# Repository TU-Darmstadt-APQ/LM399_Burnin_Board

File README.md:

# ADR1399/LM399 Burnin Board
This repository contains the [KiCad](https://www.kicad.org/) schematics and design files for test board to burn in [ADR1399](https://www.analog.com/media/en/technical-documentation/data-sheets/adr1399.pdf) and [LM399](https://www.analog.com/media/en/technical-documentation/data-sheets/199399fc.pdf) voltage references.

## Contents
- [Introduction](#introduction)
- [Design Files](#design-files)
- [Related Repositories](#related-repositories)
- [Versioning](#versioning)
- [License](#license)

## Introduction
This board can support up to 20 [ADR1399](https://www.analog.com/media/en/technical-documentation/data-sheets/adr1399.pdf) or [LM399](https://www.analog.com/media/en/technical-documentation/data-sheets/199399fc.pdf) voltage references. Using a [DD-50](https://en.wikipedia.org/wiki/D-subminiature) connector, these reference can be monitored using a multiplexer and a DMM. In combination with the [2000-SCAN SSR Replacement](https://github.com/PatrickBaus/SCAN2000) up to 10 references can be scanned using a [Keithley Model 2002](https://www.tek.com/en/products/keithley/digital-multimeter/2002-series).

## Design Files
### For production
The design files required for the PCB production and assembly can be found on the [releases](../../releases) page and include the following resources:

- Schematics as a PDF
- Gerber files
- Pick & place position files
- Bill of materials as a CSV file and also as an interactive HTML version

The latest revision of those files can be found [here](../../releases/latest).

## Related Repositories
See the following repositories for more information.

- [KiCad footprints](https://github.com/PatrickBaus/footprints.pretty)
- [KiCAD schematic libraries](https://github.com/PatrickBaus/KiCad-libraries)
- [2000-SCAN SSR Replacement](https://github.com/PatrickBaus/SCAN2000)

## Versioning
I use [SemVer](http://semver.org/) for versioning. For the versions available, see the [tags](../../tags) available for this repository.

- MAJOR versions in this context mean a breaking change to the external interface of the hardware like different connectors or functions.
- MINOR versions contain changes to the hardware that only affect the inner workings of the circuit, but otherwise the performance is unaffected.
- PATCH versions do not affect the schematics or invalidate older bill of materials. These changes may include updated components (to replace obsolete parts for example), an updated silkscreen, or fixed typos.

## License
This work is released under the CERN-OHL-W
See [https://ohwr.org/cern_ohl_w_v2.pdf](https://ohwr.org/cern_ohl_w_v2.pdf) or the included LICENSE file for more information.

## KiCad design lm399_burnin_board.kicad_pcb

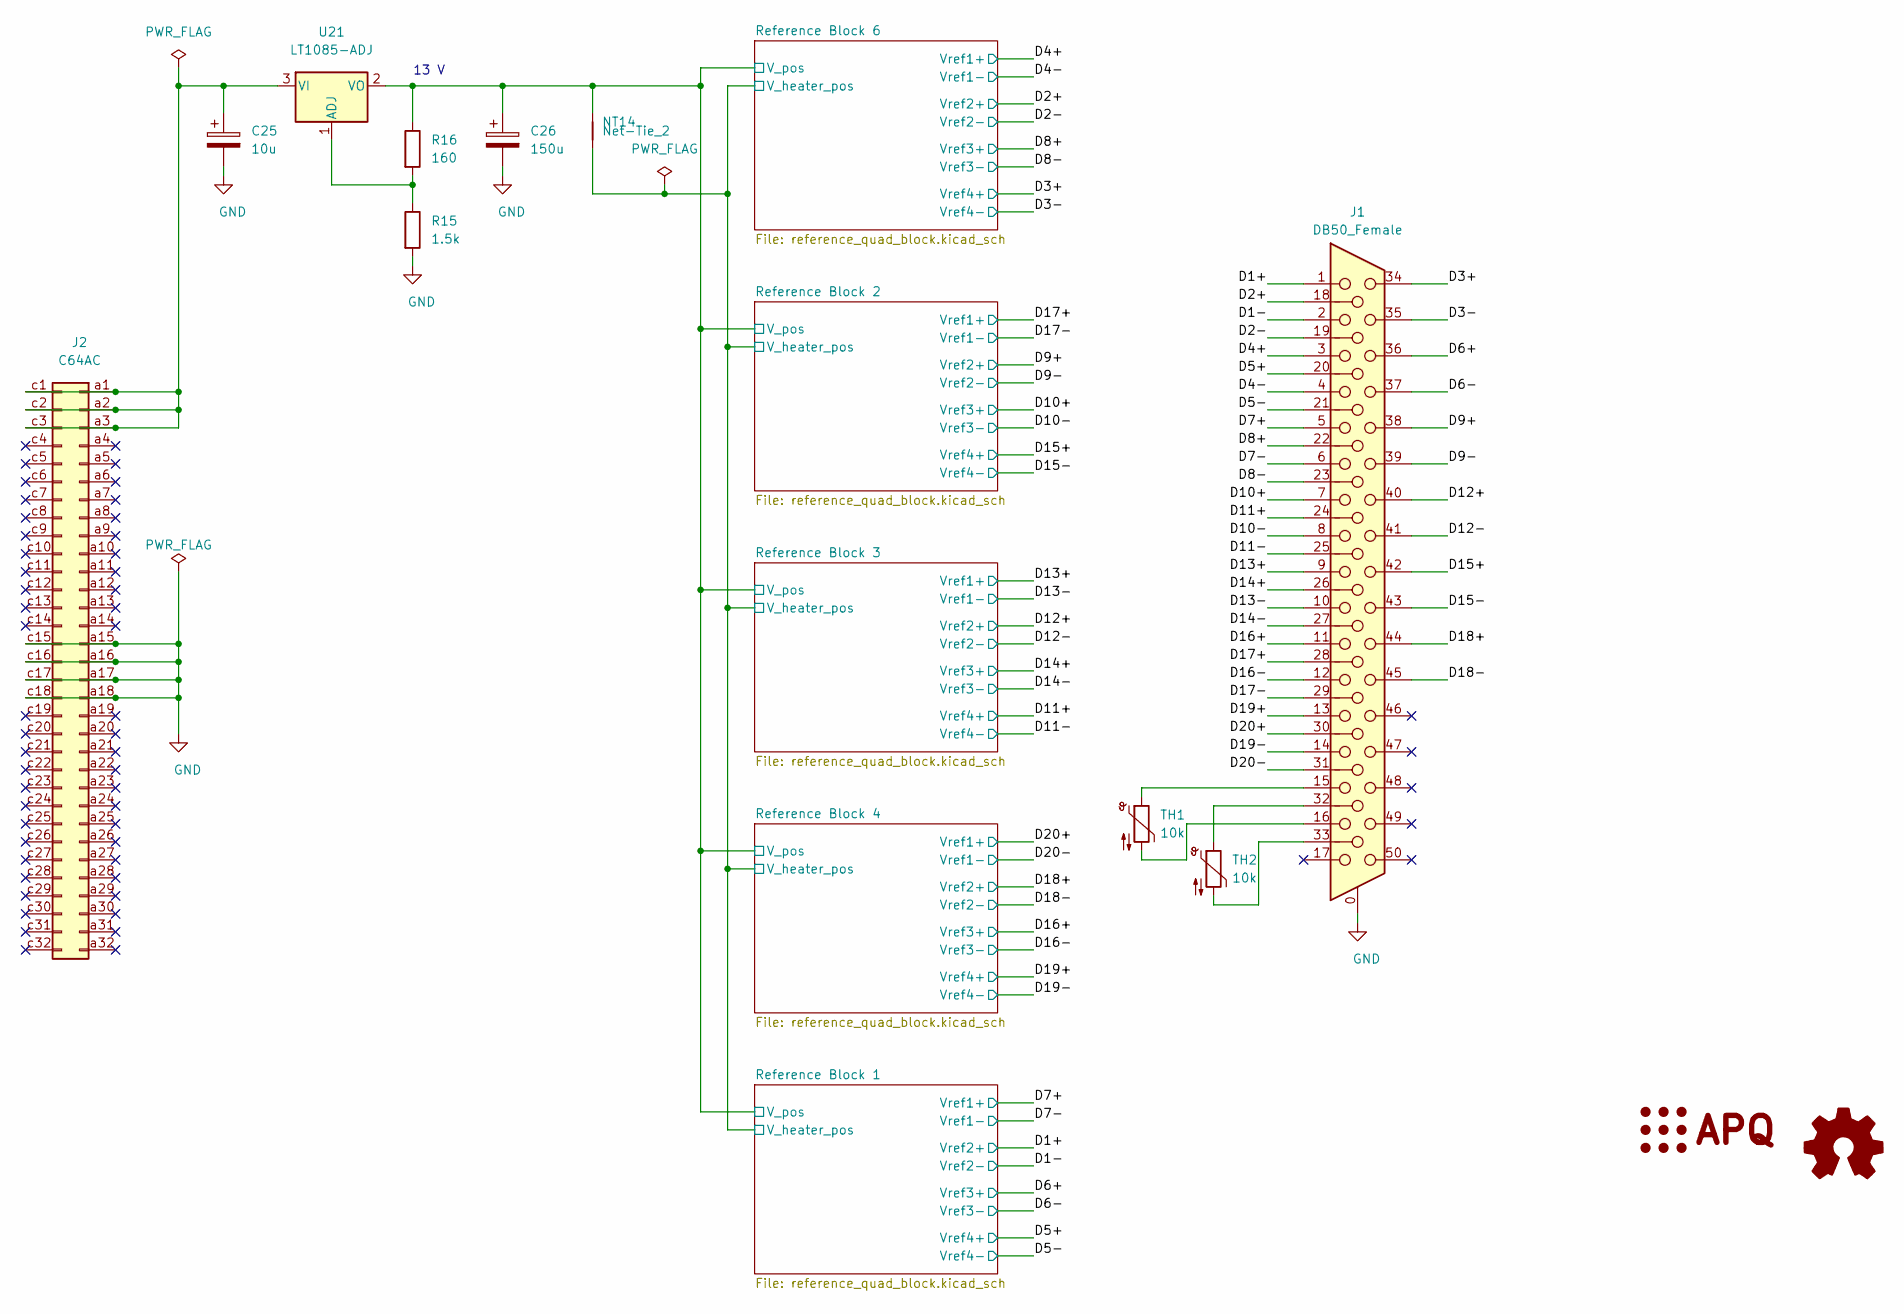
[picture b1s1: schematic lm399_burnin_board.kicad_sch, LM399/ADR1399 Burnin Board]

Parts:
C25: 10u; CP_Radial_D10.0mm_P5.00mm
C26: 150u; CP_Radial_D10.0mm_P5.00mm
J1: DB50_Female; DSUB-50_Female_Horizontal_P2.77x2.84mm_Conec_164A18969X
J2: C64AC; DIN41612_C_2x32_Male_Horizontal_THT
LOGO1: Logo_APQ; APQ-Logo
LOGO2: Logo_Open_Hardware_Small; OSHW-Logo_7.5x8mm_SilkScreen
NT14: Net-Tie_2; NetTie-2_SMD_Pad2.0mm
R15: 1.5k; R_1206_3216Metric
R16: 160; R_1206_3216Metric
TH1, TH2: 10k; R_0603_1608Metric
U21: LT1085-ADJ; TO-220-3_Vertical

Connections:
/D1+: J1.1; also elsewhere on the board
/D1-: J1.2; also elsewhere on the board
/D2+: J1.18; also elsewhere on the board
/D2-: J1.19; also elsewhere on the board
/D3+: J1.34; also elsewhere on the board
/D3-: J1.35; also elsewhere on the board
/D4+: J1.3; also elsewhere on the board
/D4-: J1.4; also elsewhere on the board
/D5+: J1.20; also elsewhere on the board
/D5-: J1.21; also elsewhere on the board
/D6+: J1.36; also elsewhere on the board
/D6-: J1.37; also elsewhere on the board
/D7+: J1.5; also elsewhere on the board
/D7-: J1.6; also elsewhere on the board
/D8+: J1.22; also elsewhere on the board
/D8-: J1.23; also elsewhere on the board
/D9+: J1.38; also elsewhere on the board
/D9-: J1.39; also elsewhere on the board
/D10+: J1.7; also elsewhere on the board
/D10-: J1.8; also elsewhere on the board
/D11+: J1.24; also elsewhere on the board
/D11-: J1.25; also elsewhere on the board
/D12+: J1.40; also elsewhere on the board
/D12-: J1.41; also elsewhere on the board
/D13+: J1.9; also elsewhere on the board
/D13-: J1.10; also elsewhere on the board
/D14+: J1.26; also elsewhere on the board
/D14-: J1.27; also elsewhere on the board
/D15+: J1.42; also elsewhere on the board
/D15-: J1.43; also elsewhere on the board
/D16+: J1.11; also elsewhere on the board
/D16-: J1.12; also elsewhere on the board
/D17+: J1.28; also elsewhere on the board
/D17-: J1.29; also elsewhere on the board
/D18+: J1.44; also elsewhere on the board
/D18-: J1.45; also elsewhere on the board
/D19+: J1.13; also elsewhere on the board
/D19-: J1.14; also elsewhere on the board
/D20+: J1.30; also elsewhere on the board
/D20-: J1.31; also elsewhere on the board
/Reference Block 1/V_heater_pos: NT14.2; also elsewhere on the board
/Reference Block 1/V_pos: C26.1, NT14.1, R16.1, U21.2 (VO); also elsewhere on the board
GND: C25.2, C26.2, J1.0 (PAD), J2.a15, J2.a16, J2.a17, J2.a18, J2.c15, J2.c16, J2.c17, J2.c18, R15.2; also elsewhere on the board
unnamed: J1.15, TH1.1
unnamed: J1.16, TH1.2
unnamed: J1.32, TH2.1
unnamed: J1.33, TH2.2
unnamed: C25.1, J2.a1, J2.a2, J2.a3, J2.c1, J2.c2, J2.c3, U21.3 (VI)
unnamed: R15.1, R16.2, U21.1 (ADJ)

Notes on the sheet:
13 V

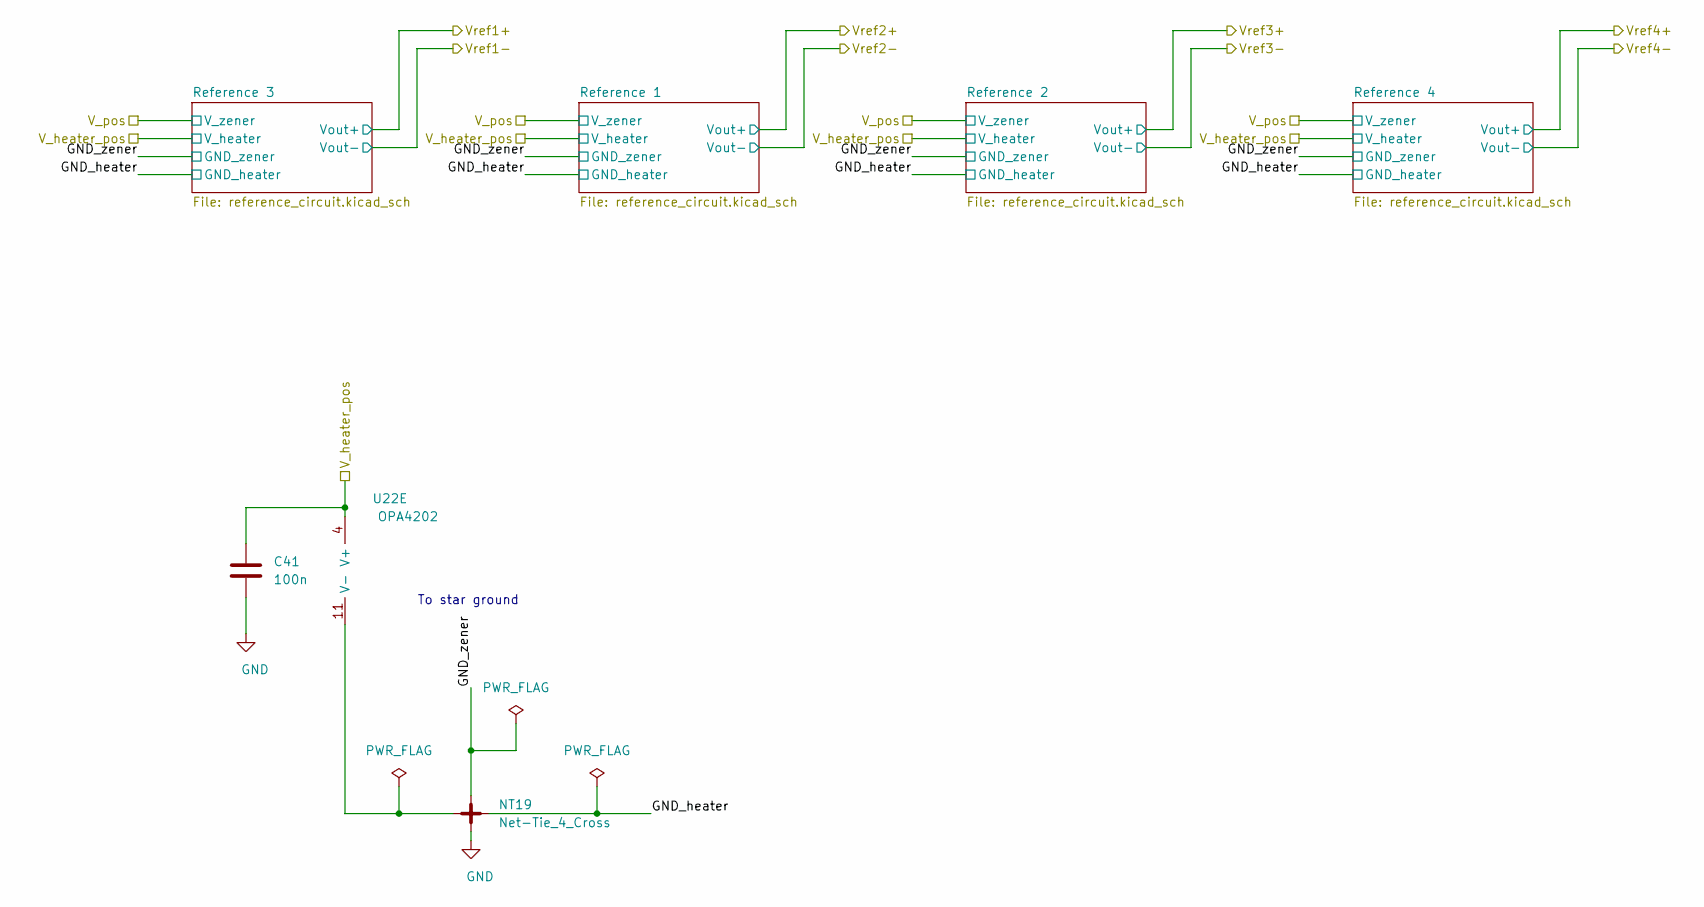
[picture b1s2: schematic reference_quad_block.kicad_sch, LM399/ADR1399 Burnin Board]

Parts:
C41: 100n; C_0603_1608Metric
NT19: Net-Tie_4_Cross; NetTie-4_SMD_Pad0.5mm
U22: OPA4202; SOIC-14_3.9x8.7mm_P1.27mm

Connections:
/Reference Block 1/V_heater_pos: C41.1, U22.4 (V+); also elsewhere on the board
/Reference Block 6/GND_heater: NT19.2; also elsewhere on the board
/Reference Block 6/GND_zener: NT19.3; also elsewhere on the board
GND: C41.2, NT19.4; also elsewhere on the board
unnamed 85: U22.8; also elsewhere on the board
unnamed 86: U22.7; also elsewhere on the board
unnamed 89: U22.14; also elsewhere on the board
unnamed 161: U22.5 (+); also elsewhere on the board
unnamed 162: U22.6 (-); also elsewhere on the board
unnamed 163: U22.10 (+); also elsewhere on the board
unnamed 164: U22.9 (-); also elsewhere on the board
unnamed 165: U22.12 (+); also elsewhere on the board
unnamed 166: U22.13 (-); also elsewhere on the board
unnamed: NT19.1, U22.11 (V-)

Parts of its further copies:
C43, C78, C82, C103: 100n; C_0603_1608Metric
NT20, NT23, NT24, NT26: Net-Tie_4_Cross; NetTie-4_SMD_Pad0.5mm
U23, U24, U25, U26: OPA4202; SOIC-14_3.9x8.7mm_P1.27mm

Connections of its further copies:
/Reference Block 1/GND_heater: NT20.2; also elsewhere on the board
/Reference Block 1/GND_zener: NT20.3; also elsewhere on the board
/Reference Block 1/V_heater_pos: C43.1, C78.1, C82.1, C103.1, U23.4 (V+), U24.4 (V+), U25.4 (V+), U26.4 (V+); also elsewhere on the board
/Reference Block 2/GND_heater: NT24.2; also elsewhere on the board
/Reference Block 2/GND_zener: NT24.3; also elsewhere on the board
/Reference Block 3/GND_heater: NT23.2; also elsewhere on the board
/Reference Block 3/GND_zener: NT23.3; also elsewhere on the board
/Reference Block 4/GND_heater: NT26.2; also elsewhere on the board
/Reference Block 4/GND_zener: NT26.3; also elsewhere on the board
GND: C43.2, C78.2, C82.2, C103.2, NT20.4, NT23.4, NT24.4, NT26.4; also elsewhere on the board
unnamed 87: U23.8; also elsewhere on the board
unnamed 88: U23.7; also elsewhere on the board
unnamed 91: U23.14; also elsewhere on the board
unnamed 92: U23.1; also elsewhere on the board
unnamed 107: U24.8; also elsewhere on the board
unnamed 108: U24.7; also elsewhere on the board
unnamed 109: U25.8; also elsewhere on the board
unnamed 110: U25.7; also elsewhere on the board
unnamed 113: U24.14; also elsewhere on the board
unnamed 114: U24.1; also elsewhere on the board
unnamed 115: U25.14; also elsewhere on the board
unnamed 116: U25.1; also elsewhere on the board
unnamed 127: U26.8; also elsewhere on the board
unnamed 128: U26.7; also elsewhere on the board
unnamed 129: U26.14; also elsewhere on the board
unnamed 130: U26.1; also elsewhere on the board
unnamed 168: U23.3 (+); also elsewhere on the board
unnamed 169: U23.2 (-); also elsewhere on the board
unnamed 170: U23.5 (+); also elsewhere on the board
unnamed 171: U23.6 (-); also elsewhere on the board
unnamed 172: U23.10 (+); also elsewhere on the board
unnamed 173: U23.9 (-); also elsewhere on the board
unnamed 174: U23.12 (+); also elsewhere on the board
unnamed 175: U23.13 (-); also elsewhere on the board
unnamed: NT20.1, U23.11 (V-)
unnamed 177: U24.3 (+); also elsewhere on the board
unnamed 178: U24.2 (-); also elsewhere on the board
unnamed 179: U24.5 (+); also elsewhere on the board
unnamed 180: U24.6 (-); also elsewhere on the board
unnamed 181: U24.10 (+); also elsewhere on the board
unnamed 182: U24.9 (-); also elsewhere on the board
unnamed 183: U24.12 (+); also elsewhere on the board
unnamed 184: U24.13 (-); also elsewhere on the board
unnamed: NT23.1, U24.11 (V-)
unnamed 186: U25.3 (+); also elsewhere on the board
unnamed 187: U25.2 (-); also elsewhere on the board
unnamed 188: U25.5 (+); also elsewhere on the board
unnamed 189: U25.6 (-); also elsewhere on the board
unnamed 190: U25.10 (+); also elsewhere on the board
unnamed 191: U25.9 (-); also elsewhere on the board
unnamed 192: U25.12 (+); also elsewhere on the board
unnamed 193: U25.13 (-); also elsewhere on the board
unnamed: NT24.1, U25.11 (V-)
unnamed 195: U26.3 (+); also elsewhere on the board
unnamed 196: U26.2 (-); also elsewhere on the board
unnamed 197: U26.5 (+); also elsewhere on the board
unnamed 198: U26.6 (-); also elsewhere on the board
unnamed 199: U26.10 (+); also elsewhere on the board
unnamed 200: U26.9 (-); also elsewhere on the board
unnamed 201: U26.12 (+); also elsewhere on the board
unnamed 202: U26.13 (-); also elsewhere on the board
unnamed: NT26.1, U26.11 (V-)

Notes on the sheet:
To star ground

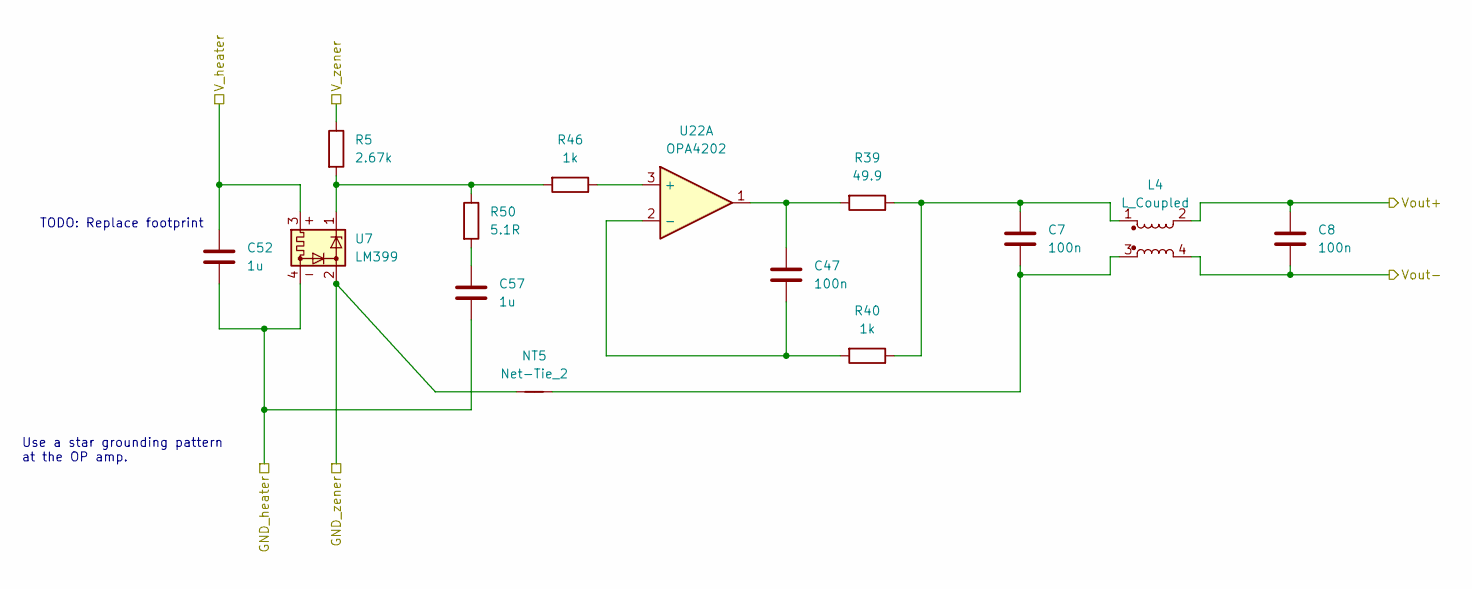
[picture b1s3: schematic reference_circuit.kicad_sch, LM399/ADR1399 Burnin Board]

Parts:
C7, C8, C47: 100n; C_1206_3216Metric
C52, C57: 1u; C_0603_1608Metric
L4: L_Coupled; L_CommonMode_EPCOS_B82790
NT5: Net-Tie_2; NET-TIE-0.25mm
R5: 2.67k; R_0805_2012Metric
R39: 49.9; R_0603_1608Metric
R40, R46: 1k; R_0603_1608Metric
R50: 5.1R; R_0603_1608Metric
U7: LM399; Analog_TO-46-4_ThermalShield_socket
U22: OPA4202; SOIC-14_3.9x8.7mm_P1.27mm

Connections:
/D4+: C8.1, L4.2; also elsewhere on the board
/D4-: C8.2, L4.4; also elsewhere on the board
/Reference Block 1/V_heater_pos: C52.1, U7.3; also elsewhere on the board
/Reference Block 1/V_pos: R5.1; also elsewhere on the board
/Reference Block 6/GND_heater: C52.2, C57.2, U7.4; also elsewhere on the board
/Reference Block 6/GND_zener: NT5.1, U7.2; also elsewhere on the board
unnamed: C7.1, L4.1, R39.1, R40.1
unnamed: C7.2, L4.3, NT5.2
unnamed 85: U22.8; also elsewhere on the board
unnamed 86: U22.7; also elsewhere on the board
unnamed 89: U22.14; also elsewhere on the board
unnamed: C47.1, R39.2, U22.1
unnamed: C57.1, R50.2
unnamed: R5.2, R46.2, R50.1, U7.1
unnamed: R46.1, U22.3 (+)
unnamed: C47.2, R40.2, U22.2 (-)
unnamed 161: U22.5 (+); also elsewhere on the board
unnamed 162: U22.6 (-); also elsewhere on the board
unnamed 163: U22.10 (+); also elsewhere on the board
unnamed 164: U22.9 (-); also elsewhere on the board
unnamed 165: U22.12 (+); also elsewhere on the board
unnamed 166: U22.13 (-); also elsewhere on the board

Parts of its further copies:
C1, C2, C3, C4, C5, C6, C9, C10, C11, C12, C13, C14, C15, C16, C17, C18, C19, C20, C21, C22, C23, C24, C27, C28, C29, C30, C39, C40, C42, C44, C46, C49, C50, C55, C56, C63, C64, C69, C70, C71, C72, C73, C74, C75, C76, C77, C79, C80, C81, C89, C90, C93, C94, C99, C100, C101, C102: 100n; C_1206_3216Metric
C31, C32, C33, C34, C35, C36, C37, C38, C45, C48, C51, C53, C54, C58, C59, C60, C61, C62, C65, C66, C67, C68, C83, C84, C85, C86, C87, C88, C91, C92, C95, C96, C97, C98, C104, C105, C106, C107: 1u; C_0603_1608Metric
L1, L2, L3, L5, L6, L7, L8, L9, L10, L11, L12, L13, L14, L15, L16, L17, L18, L19, L20: L_Coupled; L_CommonMode_EPCOS_B82790
NT1, NT2, NT3, NT4, NT6, NT7, NT8, NT9, NT10, NT11, NT12, NT13, NT15, NT16, NT17, NT18, NT21, NT22, NT25: Net-Tie_2; NET-TIE-0.25mm
R1, R2, R3, R4, R6, R7, R8, R9, R10, R11, R12, R13, R14, R17, R18, R31, R36, R69, R92: 2.67k; R_0805_2012Metric
R19, R20, R21, R22, R49, R51, R52, R53, R54, R55, R59, R82, R83, R84, R85, R86, R87, R101, R102: 5.1R; R_0603_1608Metric
R23, R24, R25, R26, R28, R30, R32, R34, R38, R42, R44, R45, R47, R48, R56, R57, R58, R60, R61, R63, R65, R68, R71, R72, R75, R76, R78, R79, R80, R81, R88, R89, R93, R95, R96, R97, R99, R100: 1k; R_0603_1608Metric
R27, R29, R33, R35, R37, R41, R43, R62, R64, R66, R67, R70, R73, R74, R77, R90, R91, R94, R98: 49.9; R_0603_1608Metric
U1, U2, U3, U4, U5, U6, U8, U9, U10, U11, U12, U13, U14, U15, U16, U17, U18, U19, U20: LM399; Analog_TO-46-4_ThermalShield_socket
U23, U24, U25, U26: OPA4202; SOIC-14_3.9x8.7mm_P1.27mm

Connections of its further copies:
/D1+: C2.1, L1.2; also elsewhere on the board
/D1-: C2.2, L1.4; also elsewhere on the board
/D2+: C4.1, L2.2; also elsewhere on the board
/D2-: C4.2, L2.4; also elsewhere on the board
/D3+: C6.1, L3.2; also elsewhere on the board
/D3-: C6.2, L3.4; also elsewhere on the board
/D5+: C10.1, L5.2; also elsewhere on the board
/D5-: C10.2, L5.4; also elsewhere on the board
/D6+: C55.1, L15.2; also elsewhere on the board
/D6-: C55.2, L15.4; also elsewhere on the board
/D7+: C12.1, L6.2; also elsewhere on the board
/D7-: C12.2, L6.4; also elsewhere on the board
/D8+: C63.1, L16.2; also elsewhere on the board
/D8-: C63.2, L16.4; also elsewhere on the board
/D9+: C14.1, L7.2; also elsewhere on the board
/D9-: C14.2, L7.4; also elsewhere on the board
/D10+: C69.1, L17.2; also elsewhere on the board
/D10-: C69.2, L17.4; also elsewhere on the board
/D11+: C16.1, L8.2; also elsewhere on the board
/D11-: C16.2, L8.4; also elsewhere on the board
/D12+: C75.1, L18.2; also elsewhere on the board
/D12-: C75.2, L18.4; also elsewhere on the board
/D13+: C18.1, L9.2; also elsewhere on the board
/D13-: C18.2, L9.4; also elsewhere on the board
/D14+: C89.1, L19.2; also elsewhere on the board
/D14-: C89.2, L19.4; also elsewhere on the board
/D15+: C20.1, L10.2; also elsewhere on the board
/D15-: C20.2, L10.4; also elsewhere on the board
/D16+: C93.1, L20.2; also elsewhere on the board
/D16-: C93.2, L20.4; also elsewhere on the board
/D17+: C22.1, L11.2; also elsewhere on the board
/D17-: C22.2, L11.4; also elsewhere on the board
/D18+: C24.1, L12.2; also elsewhere on the board
/D18-: C24.2, L12.4; also elsewhere on the board
/D19+: C28.1, L13.2; also elsewhere on the board
/D19-: C28.2, L13.4; also elsewhere on the board
/D20+: C30.1, L14.2; also elsewhere on the board
/D20-: C30.2, L14.4; also elsewhere on the board
/Reference Block 1/GND_heater: C35.2, C36.2, C37.2, C38.2, C48.2, C53.2, C54.2, C58.2, U1.4, U2.4, U5.4, U6.4; also elsewhere on the board
/Reference Block 1/GND_zener: NT1.1, NT3.1, NT4.1, NT18.1, U1.2, U2.2, U5.2, U6.2; also elsewhere on the board
/Reference Block 1/V_heater_pos: C31.1, C33.1, C35.1, C37.1, C45.1, C48.1, C54.1, C65.1, C66.1, C67.1, C68.1, C83.1, C85.1, C86.1, C88.1, C97.1, C98.1, C104.1, C106.1, U1.3, U2.3, U3.3, U4.3, U5.3, U6.3, U8.3, U9.3, U10.3, U11.3, U12.3, U13.3, U14.3, U15.3, U16.3, U17.3, U18.3, U19.3, U20.3, U23.4 (V+), U24.4 (V+), U25.4 (V+), U26.4 (V+); also elsewhere on the board
/Reference Block 1/V_pos: R1.1, R2.1, R3.1, R4.1, R6.1, R7.1, R8.1, R9.1, R10.1, R11.1, R12.1, R13.1, R14.1, R17.1, R18.1, R31.1, R36.1, R69.1, R92.1; also elsewhere on the board
/Reference Block 2/GND_heater: C61.2, C62.2, C67.2, C68.2, C86.2, C87.2, C88.2, C92.2, U9.4, U10.4, U13.4, U14.4; also elsewhere on the board
/Reference Block 2/GND_zener: NT7.1, NT9.1, NT10.1, NT22.1, U9.2, U10.2, U13.2, U14.2; also elsewhere on the board
/Reference Block 3/GND_heater: C59.2, C60.2, C65.2, C66.2, C83.2, C84.2, C85.2, C91.2, U11.4, U12.4, U15.4, U16.4; also elsewhere on the board
/Reference Block 3/GND_zener: NT8.1, NT11.1, NT12.1, NT21.1, U11.2, U12.2, U15.2, U16.2; also elsewhere on the board
/Reference Block 4/GND_heater: C95.2, C96.2, C97.2, C98.2, C104.2, C105.2, C106.2, C107.2, U17.4, U18.4, U19.4, U20.4; also elsewhere on the board
/Reference Block 4/GND_zener: NT13.1, NT15.1, NT16.1, NT25.1, U17.2, U18.2, U19.2, U20.2; also elsewhere on the board
/Reference Block 6/GND_heater: C31.2, C32.2, C33.2, C34.2, C45.2, C51.2, U3.4, U4.4, U8.4; also elsewhere on the board
/Reference Block 6/GND_zener: NT2.1, NT6.1, NT17.1, U3.2, U4.2, U8.2; also elsewhere on the board
unnamed: C1.1, L1.1, R34.1, R35.1
unnamed: C1.2, L1.3, NT1.2
unnamed: C3.1, L2.1, R29.1, R30.1
unnamed: C3.2, L2.3, NT2.2
unnamed: C5.1, L3.1, R37.1, R38.1
unnamed: C5.2, L3.3, NT6.2
unnamed: C9.1, L5.1, R41.1, R42.1
unnamed: C9.2, L5.3, NT4.2
unnamed: C11.1, L6.1, R43.1, R44.1
unnamed: C11.2, L6.3, NT3.2
unnamed: C13.1, L7.1, R67.1, R68.1
unnamed: C13.2, L7.3, NT7.2
unnamed: C15.1, L8.1, R70.1, R71.1
unnamed: C15.2, L8.3, NT12.2
unnamed: C17.1, L9.1, R72.1, R73.1
unnamed: C17.2, L9.3, NT11.2
unnamed: C19.1, L10.1, R74.1, R75.1
unnamed: C19.2, L10.3, NT10.2
unnamed: C21.1, L11.1, R76.1, R77.1
unnamed: C21.2, L11.3, NT9.2
unnamed: C23.1, L12.1, R91.1, R97.1
unnamed: C23.2, L12.3, NT13.2
unnamed: C27.1, L13.1, R94.1, R95.1
unnamed: C27.2, L13.3, NT16.2
unnamed: C29.1, L14.1, R96.1, R98.1
unnamed: C29.2, L14.3, NT15.2
unnamed: C32.1, R19.2
unnamed: C34.1, R20.2
unnamed: C36.1, R21.2
unnamed: C38.1, R22.2
unnamed 85: C39.1, R27.2; also elsewhere on the board
unnamed 86: C40.1, R29.2; also elsewhere on the board
unnamed: C42.1, R33.2, U23.8
unnamed: C44.1, R35.2, U23.7
unnamed 89: C46.1, R37.2; also elsewhere on the board
unnamed: C49.1, R41.2, U23.14
unnamed: C50.1, R43.2, U23.1
unnamed: C51.1, R49.2
unnamed: C53.1, R51.2
unnamed: C56.1, L15.1, R32.1, R33.1
unnamed: C56.2, L15.3, NT18.2
unnamed: C58.1, R52.2
unnamed: C59.1, R55.2
unnamed: C60.1, R53.2
unnamed: C61.1, R59.2
unnamed: C62.1, R54.2
unnamed: C64.1, L16.1, R27.1, R28.1
unnamed: C64.2, L16.3, NT17.2
unnamed: C70.1, L17.1, R65.1, R66.1
unnamed: C70.2, L17.3, NT22.2
unnamed: C71.1, R62.2, U24.8
unnamed: C72.1, R64.2, U24.7
unnamed: C73.1, R66.2, U25.8
unnamed: C74.1, R67.2, U25.7
unnamed: C76.1, L18.1, R63.1, R64.1
unnamed: C76.2, L18.3, NT8.2
unnamed: C77.1, R70.2, U24.14
unnamed: C79.1, R73.2, U24.1
unnamed: C80.1, R74.2, U25.14
unnamed: C81.1, R77.2, U25.1
unnamed: C84.1, R82.2
unnamed: C87.1, R84.2
unnamed: C90.1, L19.1, R61.1, R62.1
unnamed: C90.2, L19.3, NT21.2
unnamed: C91.1, R83.2
unnamed: C92.1, R85.2
unnamed: C94.1, L20.1, R90.1, R93.1
unnamed: C94.2, L20.3, NT25.2
unnamed: C95.1, R87.2
unnamed: C96.1, R86.2
unnamed: C99.1, R90.2, U26.8
unnamed: C100.1, R91.2, U26.7
unnamed: C101.1, R94.2, U26.14
unnamed: C102.1, R98.2, U26.1
unnamed: C105.1, R101.2
unnamed: C107.1, R102.2
unnamed: R1.2, R21.1, R25.2, U2.1
unnamed: R3.2, R48.2, R52.1, U5.1
unnamed: R4.2, R47.2, R51.1, U6.1
unnamed: R10.2, R81.2, R85.1, U13.1
unnamed: R11.2, R80.2, R84.1, U14.1
unnamed: R12.2, R79.2, R83.1, U15.1
unnamed: R13.2, R78.2, R82.1, U16.1
unnamed: R14.2, R87.1, R88.2, U18.1
unnamed: R2.2, R19.1, R23.2, U4.1
unnamed: R20.1, R24.2, R31.2, U3.1
unnamed: R22.1, R26.2, R36.2, U1.1
unnamed: R6.2, R45.2, R49.1, U8.1
unnamed: R8.2, R53.1, R57.2, U11.1
unnamed: R54.1, R60.2, R69.2, U9.1
unnamed: R9.2, R55.1, R56.2, U12.1
unnamed: R7.2, R58.2, R59.1, U10.1
unnamed: R86.1, R89.2, R92.2, U17.1
unnamed: R17.2, R100.2, R102.1, U19.1
unnamed: R18.2, R99.2, R101.1, U20.1
unnamed 161: R24.1; also elsewhere on the board
unnamed 162: C40.2, R30.2; also elsewhere on the board
unnamed 163: R23.1; also elsewhere on the board
unnamed 164: C39.2, R28.2; also elsewhere on the board
unnamed 165: R45.1; also elsewhere on the board
unnamed 166: C46.2, R38.2; also elsewhere on the board
unnamed: R48.1, U23.3 (+)
unnamed: C50.2, R44.2, U23.2 (-)
unnamed: R26.1, U23.5 (+)
unnamed: C44.2, R34.2, U23.6 (-)
unnamed: R25.1, U23.10 (+)
unnamed: C42.2, R32.2, U23.9 (-)
unnamed: R47.1, U23.12 (+)
unnamed: C49.2, R42.2, U23.13 (-)
unnamed 176: U23.11 (V-); also elsewhere on the board
unnamed: R79.1, U24.3 (+)
unnamed: C79.2, R72.2, U24.2 (-)
unnamed: R57.1, U24.5 (+)
unnamed: C72.2, R63.2, U24.6 (-)
unnamed: R56.1, U24.10 (+)
unnamed: C71.2, R61.2, U24.9 (-)
unnamed: R78.1, U24.12 (+)
unnamed: C77.2, R71.2, U24.13 (-)
unnamed 185: U24.11 (V-); also elsewhere on the board
unnamed: R81.1, U25.3 (+)
unnamed: C81.2, R76.2, U25.2 (-)
unnamed: R60.1, U25.5 (+)
unnamed: C74.2, R68.2, U25.6 (-)
unnamed: R58.1, U25.10 (+)
unnamed: C73.2, R65.2, U25.9 (-)
unnamed: R80.1, U25.12 (+)
unnamed: C80.2, R75.2, U25.13 (-)
unnamed 194: U25.11 (V-); also elsewhere on the board
unnamed: R100.1, U26.3 (+)
unnamed: C102.2, R96.2, U26.2 (-)
unnamed: R89.1, U26.5 (+)
unnamed: C100.2, R97.2, U26.6 (-)
unnamed: R88.1, U26.10 (+)
unnamed: C99.2, R93.2, U26.9 (-)
unnamed: R99.1, U26.12 (+)
unnamed: C101.2, R95.2, U26.13 (-)
unnamed 203: U26.11 (V-); also elsewhere on the board

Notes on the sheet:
TODO: Replace footprint
Use a star grounding pattern at the OP amp.

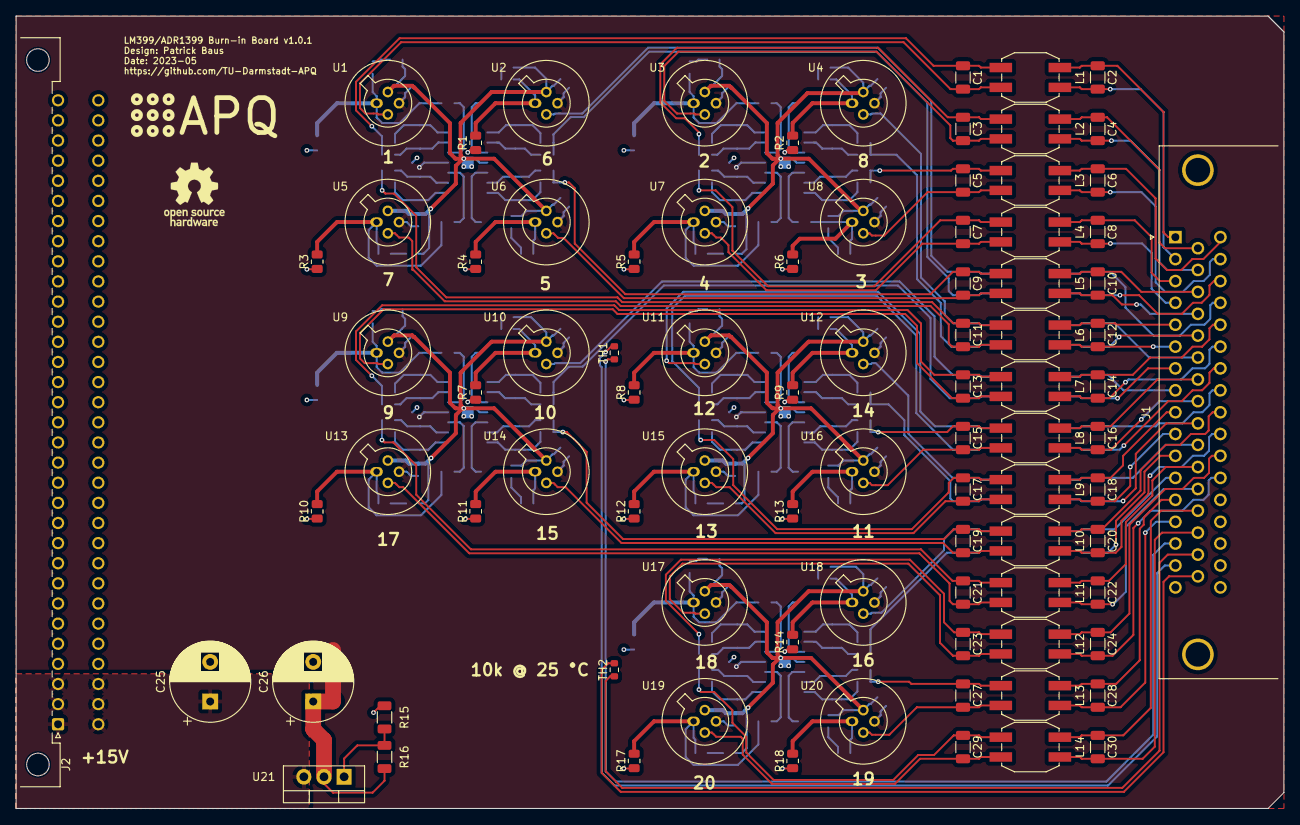
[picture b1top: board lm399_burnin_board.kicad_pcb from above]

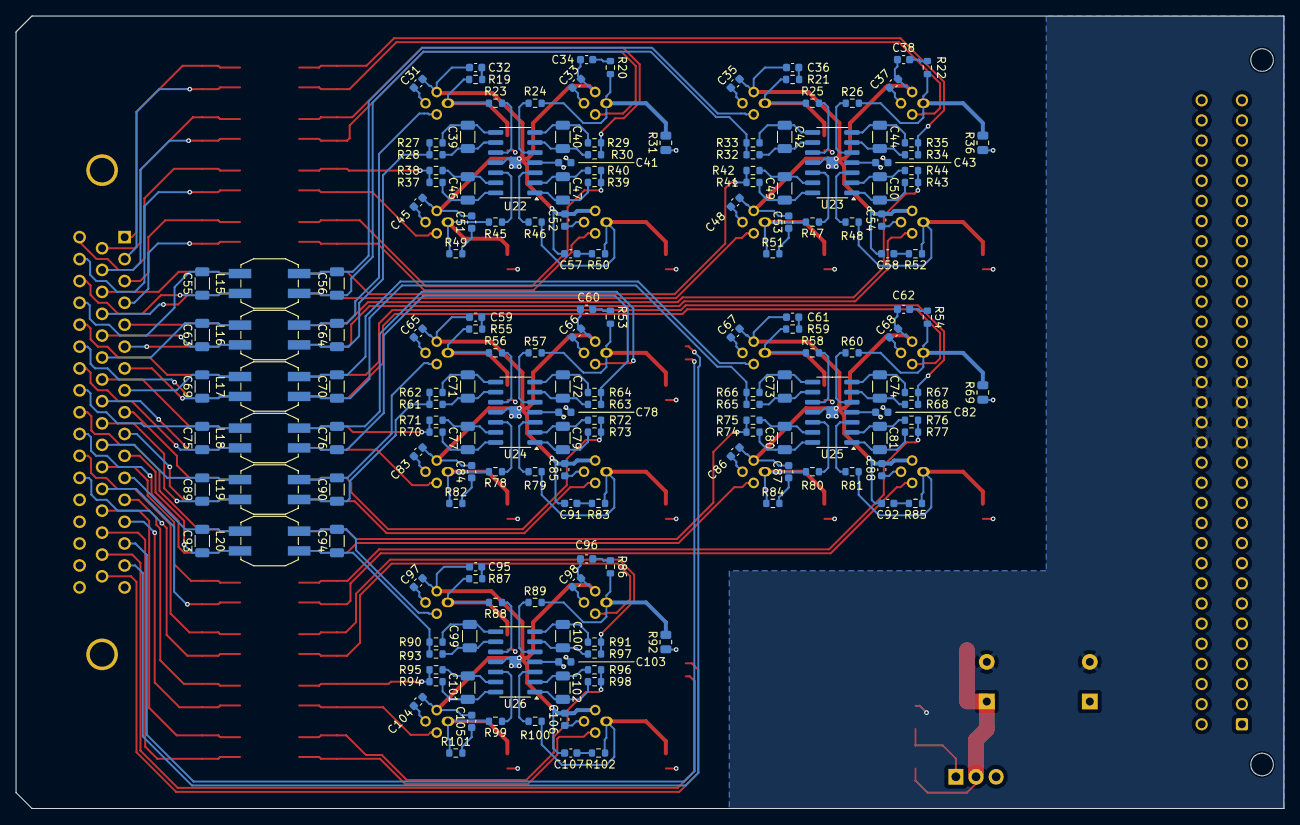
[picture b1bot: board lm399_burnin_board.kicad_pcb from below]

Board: 4 copper layers, 160.0 x 100.0 mm, 287 parts (182 on the bottom side), 204 nets.

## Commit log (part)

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2023-05-26 Add License file
2023-05-26 cleanup
2023-05-27 Fixed PCB date
2024-11-21 Updated license to CERN OHL-W v2.0
2024-11-21 Updated license to CERN OHL-W v2.0 (#1)
2024-11-21 Update KiCad to version 8
2024-11-21 Update KiCad to version 8 (#2)
2024-11-21 Renamed source files to lm399_burnin_board.*
2024-11-21 Renamed source files to lm399_burnin_board.* (#3)
2024-11-21 Updated libs
2024-11-21 Updated libs (#4)
2024-11-21 Updated references to follow geographical rules
2024-11-21 Update stackup info
2024-11-21 Fixed footprints
2024-11-21 Updated stackup
2024-11-21 Update references (#5)
    * Updated references to follow geographical rules
    * Updated stackup
2024-11-21 Added CI
2024-11-21 Added RoHS info
2024-11-21 Fixed silkscreen labels
2024-11-21 Updated symbols
2024-11-21 Added CI (#6)
    * Added CI
    * Added RoHS info
    * Fixed silkscreen labels
2024-11-21 Added readme
2024-11-21 Add readme (#7)
    * Added readme
2024-11-21 Bump version to 1.0.2
2025-11-26 Bump libraries from `80d58ef` to `ba5563d`
    Bumps [libraries](https://github.com/PatrickBaus/KiCad-libraries) from `80d58ef` to `ba5563d`.
    - [Commits](https://github.com/PatrickBaus/KiCad-libraries/compare/80d58efa29fc28aa49b090516bd5b7168ac740c8...ba5563d66c23dea06d561adcb039ddac5a03efdf)
    ---
    updated-dependencies:
    - dependency-name: libraries
    dependency-version: ba5563d66c23dea06d561adcb039ddac5a03efdf
2025-11-26 Bump libraries from `80d58ef` to `ba5563d` (#8)
    Bumps [libraries](https://github.com/PatrickBaus/KiCad-libraries) from `80d58ef` to `ba5563d`.
    - [Commits](https://github.com/PatrickBaus/KiCad-libraries/compare/80d58efa29fc28aa49b090516bd5b7168ac740c8...ba5563d66c23dea06d561adcb039ddac5a03efdf)
    ---
    updated-dependencies:
    - dependency-name: libraries
    dependency-version: ba5563d66c23dea06d561adcb039ddac5a03efdf
2025-12-17 Bump libraries from `ba5563d` to `d79317d`
    Bumps [libraries](https://github.com/PatrickBaus/KiCad-libraries) from `ba5563d` to `d79317d`.
    - [Commits](https://github.com/PatrickBaus/KiCad-libraries/compare/ba5563d66c23dea06d561adcb039ddac5a03efdf...d79317d926704a58090a36fac06bfafa731a048b)
    ---
    updated-dependencies:
    - dependency-name: libraries
    dependency-version: d79317d926704a58090a36fac06bfafa731a048b
2025-12-17 Bump libraries from `ba5563d` to `d79317d` (#9)
    Bumps [libraries](https://github.com/PatrickBaus/KiCad-libraries) from `ba5563d` to `d79317d`.
    - [Commits](https://github.com/PatrickBaus/KiCad-libraries/compare/ba5563d66c23dea06d561adcb039ddac5a03efdf...d79317d926704a58090a36fac06bfafa731a048b)
    ---
    updated-dependencies:
    - dependency-name: libraries
    dependency-version: d79317d926704a58090a36fac06bfafa731a048b
2026-02-09 Bump libraries from `d79317d` to `4179135`
    Bumps [libraries](https://github.com/PatrickBaus/KiCad-libraries) from `d79317d` to `4179135`.
    - [Commits](https://github.com/PatrickBaus/KiCad-libraries/compare/d79317d926704a58090a36fac06bfafa731a048b...41791358010d2de5d2401e25bd30de257630acf6)
    ---
    updated-dependencies:
    - dependency-name: libraries
    dependency-version: 41791358010d2de5d2401e25bd30de257630acf6
2026-02-09 Bump libraries from `d79317d` to `4179135` (#10)
    Bumps [libraries](https://github.com/PatrickBaus/KiCad-libraries) from `d79317d` to `4179135`.
    - [Commits](https://github.com/PatrickBaus/KiCad-libraries/compare/d79317d926704a58090a36fac06bfafa731a048b...41791358010d2de5d2401e25bd30de257630acf6)
    ---
    updated-dependencies:
    - dependency-name: libraries
    dependency-version: 41791358010d2de5d2401e25bd30de257630acf6
2026-04-30 [gha] Bump actions/upload-artifact from 4 to 7
    Bumps [actions/upload-artifact](https://github.com/actions/upload-artifact) from 4 to 7.
    - [Release notes](https://github.com/actions/upload-artifact/releases)
    - [Commits](https://github.com/actions/upload-artifact/compare/v4...v7)
    ---
    updated-dependencies:
    - dependency-name: actions/upload-artifact
2026-04-30 [gha] Bump actions/checkout from 4 to 6
    Bumps [actions/checkout](https://github.com/actions/checkout) from 4 to 6.
    - [Release notes](https://github.com/actions/checkout/releases)
    - [Changelog](https://github.com/actions/checkout/blob/main/CHANGELOG.md)
    - [Commits](https://github.com/actions/checkout/compare/v4...v6)
    ---
    updated-dependencies:
2026-04-30 [gha] Bump actions/download-artifact from 4 to 8
    Bumps [actions/download-artifact](https://github.com/actions/download-artifact) from 4 to 8.
    - [Release notes](https://github.com/actions/download-artifact/releases)
    - [Commits](https://github.com/actions/download-artifact/compare/v4...v8)
    ---
    updated-dependencies:
    - dependency-name: actions/download-artifact
2026-04-30 [gha] Bump actions/upload-artifact from 4 to 7 (#11)
    Bumps [actions/upload-artifact](https://github.com/actions/upload-artifact) from 4 to 7.
    - [Release notes](https://github.com/actions/upload-artifact/releases)
    - [Commits](https://github.com/actions/upload-artifact/compare/v4...v7)
    ---
    updated-dependencies:
    - dependency-name: actions/upload-artifact
2026-04-30 [gha] Bump actions/checkout from 4 to 6 (#12)
    Bumps [actions/checkout](https://github.com/actions/checkout) from 4 to 6.
    - [Release notes](https://github.com/actions/checkout/releases)
    - [Changelog](https://github.com/actions/checkout/blob/main/CHANGELOG.md)
    - [Commits](https://github.com/actions/checkout/compare/v4...v6)
    ---
    updated-dependencies:
2026-04-30 [gha] Bump actions/download-artifact from 4 to 8 (#13)
    Bumps [actions/download-artifact](https://github.com/actions/download-artifact) from 4 to 8.
    - [Release notes](https://github.com/actions/download-artifact/releases)
    - [Commits](https://github.com/actions/download-artifact/compare/v4...v8)
    ---
    updated-dependencies:
    - dependency-name: actions/download-artifact
2026-06-19 [gha] Bump actions/checkout from 6 to 7
    Bumps [actions/checkout](https://github.com/actions/checkout) from 6 to 7.
    - [Release notes](https://github.com/actions/checkout/releases)
    - [Changelog](https://github.com/actions/checkout/blob/main/CHANGELOG.md)
    - [Commits](https://github.com/actions/checkout/compare/v6...v7)
    ---
    updated-dependencies:
2026-06-19 [gha] Bump actions/checkout from 6 to 7 (#14)
    Bumps [actions/checkout](https://github.com/actions/checkout) from 6 to 7.
    - [Release notes](https://github.com/actions/checkout/releases)
    - [Changelog](https://github.com/actions/checkout/blob/main/CHANGELOG.md)
    - [Commits](https://github.com/actions/checkout/compare/v6...v7)
    ---
    updated-dependencies:

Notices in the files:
lm399_burnin_board.kicad_pcb:
Copyright (©) 2021, Patrick Baus
Licensed under CERN OHL-W v2.0
